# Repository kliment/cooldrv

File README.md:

Motor driver using DRV8825, originally designed in Eagle, now converted to KiCAD format.

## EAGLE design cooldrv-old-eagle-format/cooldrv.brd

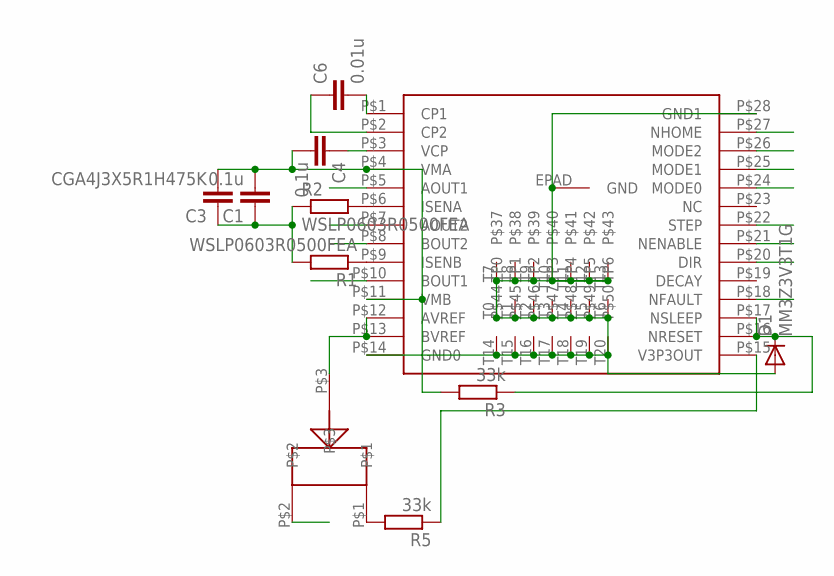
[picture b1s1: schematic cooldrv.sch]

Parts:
C1: 0.1u; C0603
C3: CGA4J3X5R1H475K; C0805K
C4: 0.1u; C0603K
C6: 0.01u; C0603
D1: MM3Z3V3T1G; SOD323-R
R1, R2: WSLP0603R0500FEA; 0805C
R3, R5: 33k; R0603
U$1: DRV8825; ETSSOP28
U$2: EVM-3YSX50B14; TRIMMER3MM

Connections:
A1: U$1.P$5 (AOUT1)
A2: U$1.P$7 (AOUT2)
B1: U$1.P$10 (BOUT1)
B2: U$1.P$8 (BOUT2)
DIR: U$1.P$20 (DIR)
EN: U$1.P$21 (NENABLE)
FAULT: U$1.P$18 (NFAULT)
GND: C1.1, C3.1, D1.A, R1.2, R2.1, U$1.EPAD (GND), U$1.P$14 (GND0), U$1.P$28 (GND1), U$1.T0 (TP0), U$1.T1 (TP1), U$1.T2 (TP2), U$1.T3 (TP3), U$1.T4 (TP4), U$1.T5 (TP5), U$1.T6 (TP6), U$1.T7, U$1.T8, U$1.T9, U$1.T10, U$1.T11, U$1.T12, U$1.T13, U$1.T14, U$1.T15, U$1.T16, U$1.T17, U$1.T18, U$1.T19, U$1.T20, U$2.P$2
HOME: U$1.P$27 (NHOME)
MS1: U$1.P$24 (MODE0)
MS2: U$1.P$25 (MODE1)
MS3: U$1.P$26 (MODE2)
unnamed: D1.C, R3.1, U$1.P$16 (NRESET), U$1.P$17 (NSLEEP)
unnamed: R2.2, U$1.P$6 (ISENA)
unnamed: R1.1, U$1.P$9 (ISENB)
unnamed: C6.2, U$1.P$1 (CP1)
unnamed: C6.1, U$1.P$2 (CP2)
unnamed: C4.1, U$1.P$3 (VCP)
unnamed: R5.2, U$2.P$1
unnamed: R5.1, U$1.P$15 (V3P3OUT)
REF: U$1.P$12 (AVREF), U$1.P$13 (BVREF), U$2.P$3
STEP: U$1.P$22 (STEP)
VMOT: C1.2, C3.2, C4.2, R3.2, U$1.P$4 (VMA), U$1.P$11 (VMB)

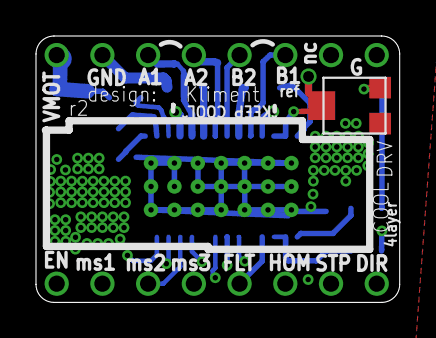
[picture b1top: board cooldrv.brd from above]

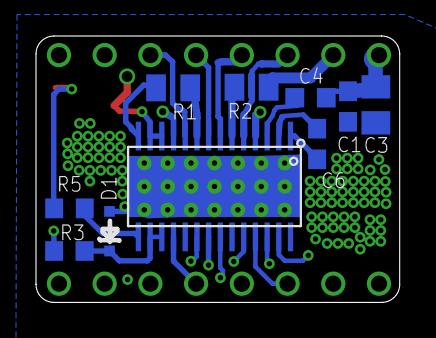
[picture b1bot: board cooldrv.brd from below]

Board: 4 copper layers, 20.2 x 14.8 mm, 11 parts (10 on the bottom side), 11 nets.

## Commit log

2020-09-14 Move Eagle files into separate directory
2020-09-14 Convert to Kicad format and re-generate production files and images
2020-09-14 Add README
